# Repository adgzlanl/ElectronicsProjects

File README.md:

# ElectronicsProjects
includes electronics schematics ,PCB Layout Circuits

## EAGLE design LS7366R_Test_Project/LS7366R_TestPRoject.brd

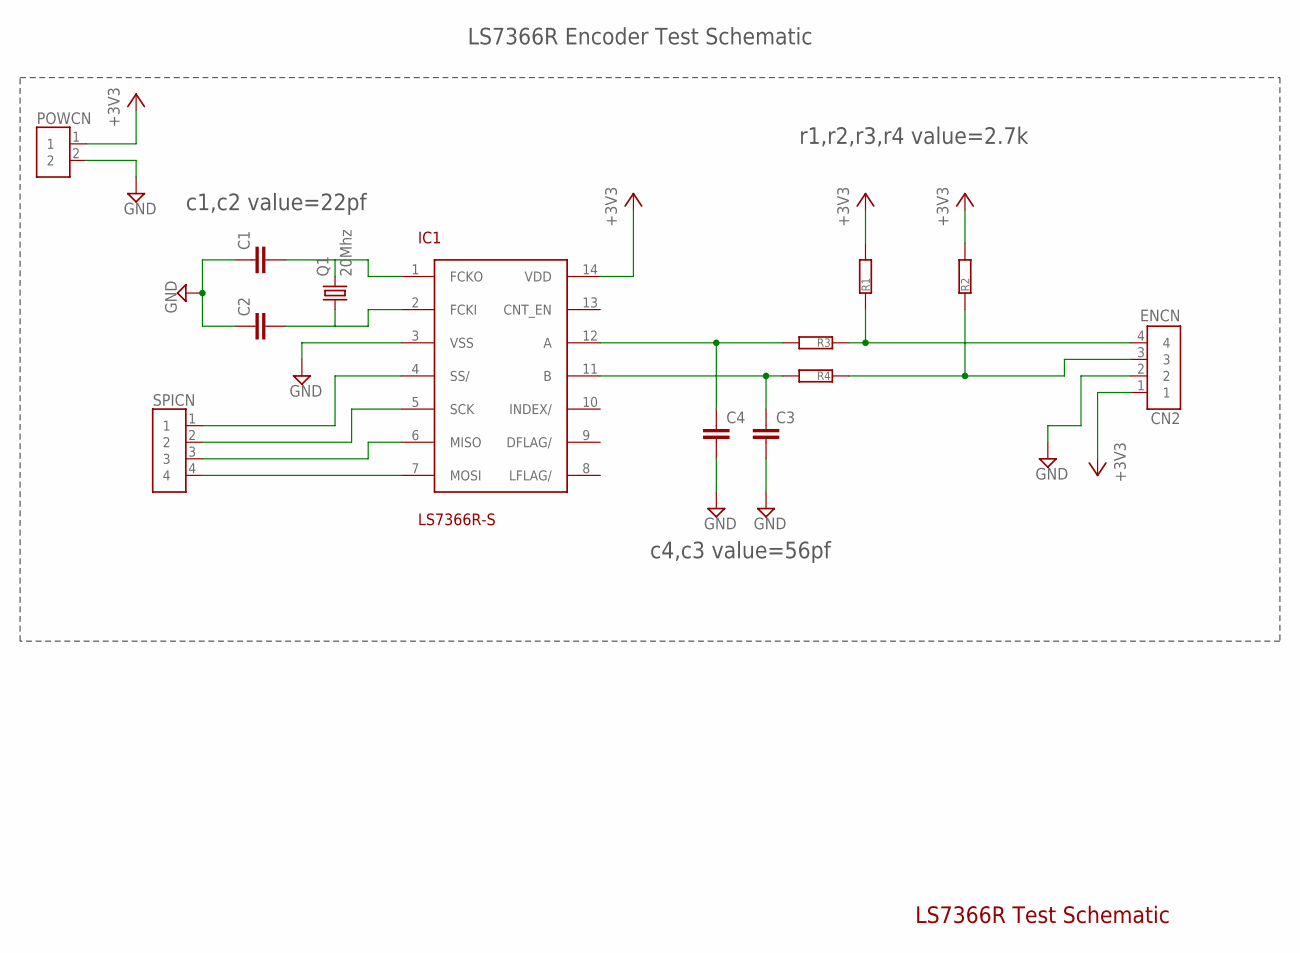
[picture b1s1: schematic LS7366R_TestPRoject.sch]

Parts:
C1, C2: 22pf; L0_0603
C3, C4: 56pf; L0_0603
CN2: ENCN; L0_TUNIK-4
IC1: LS7366R-S; SOIC-14
POWCN: TUNIK-2PIN; L0_TUNIK-2
Q1: 20Mhz; L0_ABM3
R1, R2, R3, R4: 2.7k; L0_0603
SPICN: TUNIK-4PIN; L0_TUNIK-4

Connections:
+3V3: CN2.1, IC1.14 (VDD), POWCN.1, R1.2, R2.2
GND: C1.2, C2.2, C3.1, C4.1, CN2.2, IC1.3 (VSS), POWCN.2
unnamed: CN2.4, R1.1, R3.1
unnamed: CN2.3, R2.1, R4.1
unnamed: C4.2, IC1.12 (A), R3.2
unnamed: C3.2, IC1.11 (B), R4.2
unnamed: C1.1, IC1.1 (FCKO), Q1.2
unnamed: C2.1, IC1.2 (FCKI), Q1.1
unnamed: IC1.4 (SS/), SPICN.1
unnamed: IC1.5 (SCK), SPICN.2
unnamed: IC1.6 (MISO), SPICN.3
unnamed: IC1.7 (MOSI), SPICN.4

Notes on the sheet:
LS7366R Test Schematic
c1,c2 value=22pf
c4,c3 value=56pf
r1,r2,r3,r4 value=2.7k
LS7366R Encoder Test Schematic

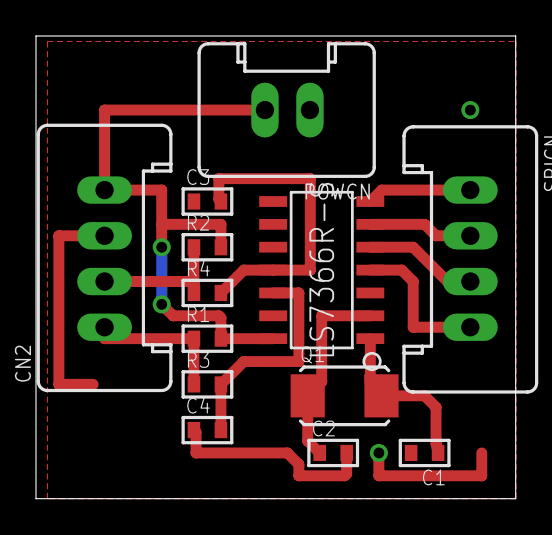
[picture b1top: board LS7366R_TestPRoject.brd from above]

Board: 2 copper layers, 26.7 x 25.7 mm, 13 parts (0 on the bottom side), 12 nets.

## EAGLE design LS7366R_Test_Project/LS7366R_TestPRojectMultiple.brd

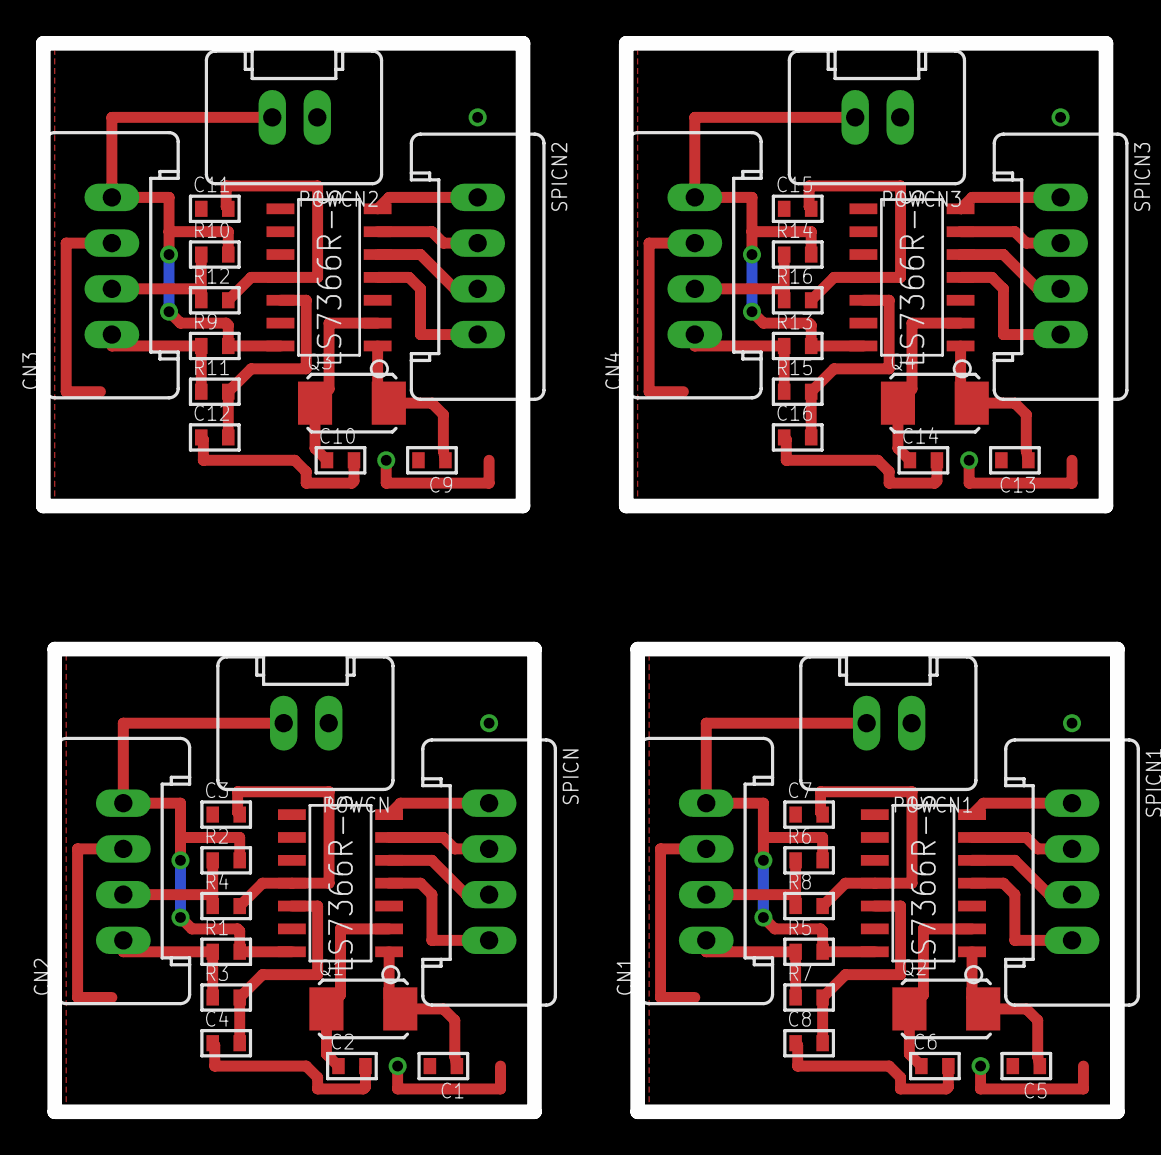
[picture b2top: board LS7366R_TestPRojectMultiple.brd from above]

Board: 2 copper layers, 59.7 x 59.4 mm, 52 parts (0 on the bottom side), 48 nets.

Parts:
C1, C2, C5, C6, C9, C10, C13, C14: 22pf; L0_0603
C3, C4, C7, C8, C11, C12, C15, C16: 56pf; L0_0603
CN1, CN2, CN3, CN4: ENCN; L0_TUNIK-4
IC1, IC2, IC3, IC4: LS7366R-S; SOIC-14
POWCN, POWCN1, POWCN2, POWCN3: L0_TUNIK-2
Q1, Q2, Q3, Q4: 20Mhz; L0_ABM3
R1, R2, R3, R4, R5, R6, R7, R8, R9, R10, R11, R12, R13, R14, R15, R16: 2.7k; L0_0603
SPICN, SPICN1, SPICN2, SPICN3: L0_TUNIK-4

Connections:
+3V1: CN1.1, IC2.14, POWCN1.1, R5.2, R6.2
+3V2: CN3.1, IC3.14, POWCN2.1, R9.2, R10.2
+3V3: CN2.1, IC1.14, POWCN.1, R1.2, R2.2
+3V4: CN4.1, IC4.14, POWCN3.1, R13.2, R14.2
GND: C1.2, C2.2, C3.1, C4.1, CN2.2, IC1.3, POWCN.2
GND1: C5.2, C6.2, C7.1, C8.1, CN1.2, IC2.3, POWCN1.2
GND2: C9.2, C10.2, C11.1, C12.1, CN3.2, IC3.3, POWCN2.2
GND3: C13.2, C14.2, C15.1, C16.1, CN4.2, IC4.3, POWCN3.2
unnamed: CN2.4, R1.1, R3.1
unnamed: CN2.3, R2.1, R4.1
unnamed: C4.2, IC1.12, R3.2
unnamed: C3.2, IC1.11, R4.2
unnamed: C1.1, IC1.1, Q1.2
unnamed: C2.1, IC1.2, Q1.1
unnamed: CN1.4, R5.1, R7.1
unnamed: CN1.3, R6.1, R8.1
unnamed: IC1.4, SPICN.1
unnamed: IC1.5, SPICN.2
unnamed: IC1.6, SPICN.3
unnamed: IC1.7, SPICN.4
unnamed: C8.2, IC2.12, R7.2
unnamed: C7.2, IC2.11, R8.2
unnamed: C5.1, IC2.1, Q2.2
unnamed: C6.1, IC2.2, Q2.1
unnamed: IC2.4, SPICN1.1
unnamed: IC2.5, SPICN1.2
unnamed: IC2.6, SPICN1.3
unnamed: IC2.7, SPICN1.4
unnamed: CN3.4, R9.1, R11.1
unnamed: CN3.3, R10.1, R12.1
unnamed: C12.2, IC3.12, R11.2
unnamed: C11.2, IC3.11, R12.2
unnamed: C9.1, IC3.1, Q3.2
unnamed: C10.1, IC3.2, Q3.1
unnamed: IC3.4, SPICN2.1
unnamed: IC3.5, SPICN2.2
unnamed: IC3.6, SPICN2.3
unnamed: IC3.7, SPICN2.4
unnamed: CN4.4, R13.1, R15.1
unnamed: CN4.3, R14.1, R16.1
unnamed: C16.2, IC4.12, R15.2
unnamed: C15.2, IC4.11, R16.2
unnamed: C13.1, IC4.1, Q4.2
unnamed: C14.1, IC4.2, Q4.1
unnamed: IC4.4, SPICN3.1
unnamed: IC4.5, SPICN3.2
unnamed: IC4.6, SPICN3.3
unnamed: IC4.7, SPICN3.4

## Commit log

2016-05-13 This Project in orders to test LS7366R IC
2016-05-13 Added Multiple PCB Board
2016-05-13 added PDF for manufacturing
2016-05-16 no message
